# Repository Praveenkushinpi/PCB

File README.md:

# PCB
This is where i will share my learning in PCB designing  
#PLANE
✈️ Plane - My First PCB Design
Plane is my first custom PCB project, designed to simulate the lighting effect found on airplane wings. This simple circuit includes resistors, capacitors, and LEDs arranged to visually mimic wingtip lights, often used for orientation and safety on real aircraft.

🔧 Components Used

4 × Resistors 

2 × Capacitors 

2 × LEDs

2 × PNP transistors 
Power Source – 3V or 5V (battery or USB)

🔌 Functionality

The PCB is designed to:

Power multiple LEDs representing plane wing lights

Include basic passive components for voltage control and stability

Be compact and simple enough for beginners to fabricate and solder

The lights can be statically on or modified later with microcontroller logic to blink in patterns.

📐 Design Notes
Designed using [KiCad](https://www.kicad.org/)

All traces are routed for minimal interference

The layout resembles a small aircraft outline, with LEDs placed at the ends to simulate left and right wings

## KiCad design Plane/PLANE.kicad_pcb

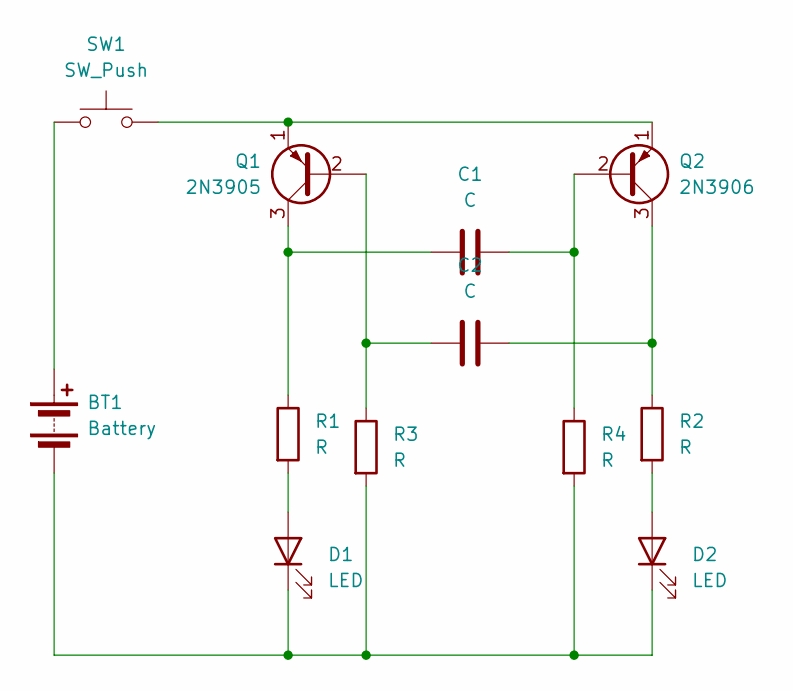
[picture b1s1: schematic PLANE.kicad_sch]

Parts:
BT1: Battery; BatteryHolder_Keystone_3034_1x20mm
C1, C2: C; CP_Radial_D8.0mm_P5.00mm
D1, D2: LED; LED_D5.0mm
Q1: 2N3905; TO-92_Inline
Q2: 2N3906; TO-92_Inline
R1, R2, R3, R4: R; R_Axial_DIN0207_L6.3mm_D2.5mm_P7.62mm_Horizontal
SW1: SW_Push; SW_PUSH_6mm

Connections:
unnamed: BT1.1 (+), SW1.1
unnamed: BT1.2 (-), D1.1 (K), D2.1 (K), R3.2, R4.2
unnamed: D1.2 (A), R1.2
unnamed: D2.2 (A), R2.2
unnamed: C2.2, Q1.2 (B), R3.1
unnamed: C1.1, Q1.3 (C), R1.1
unnamed: Q1.1 (E), Q2.1 (E), SW1.2
unnamed: C1.2, Q2.2 (B), R4.1
unnamed: C2.1, Q2.3 (C), R2.1

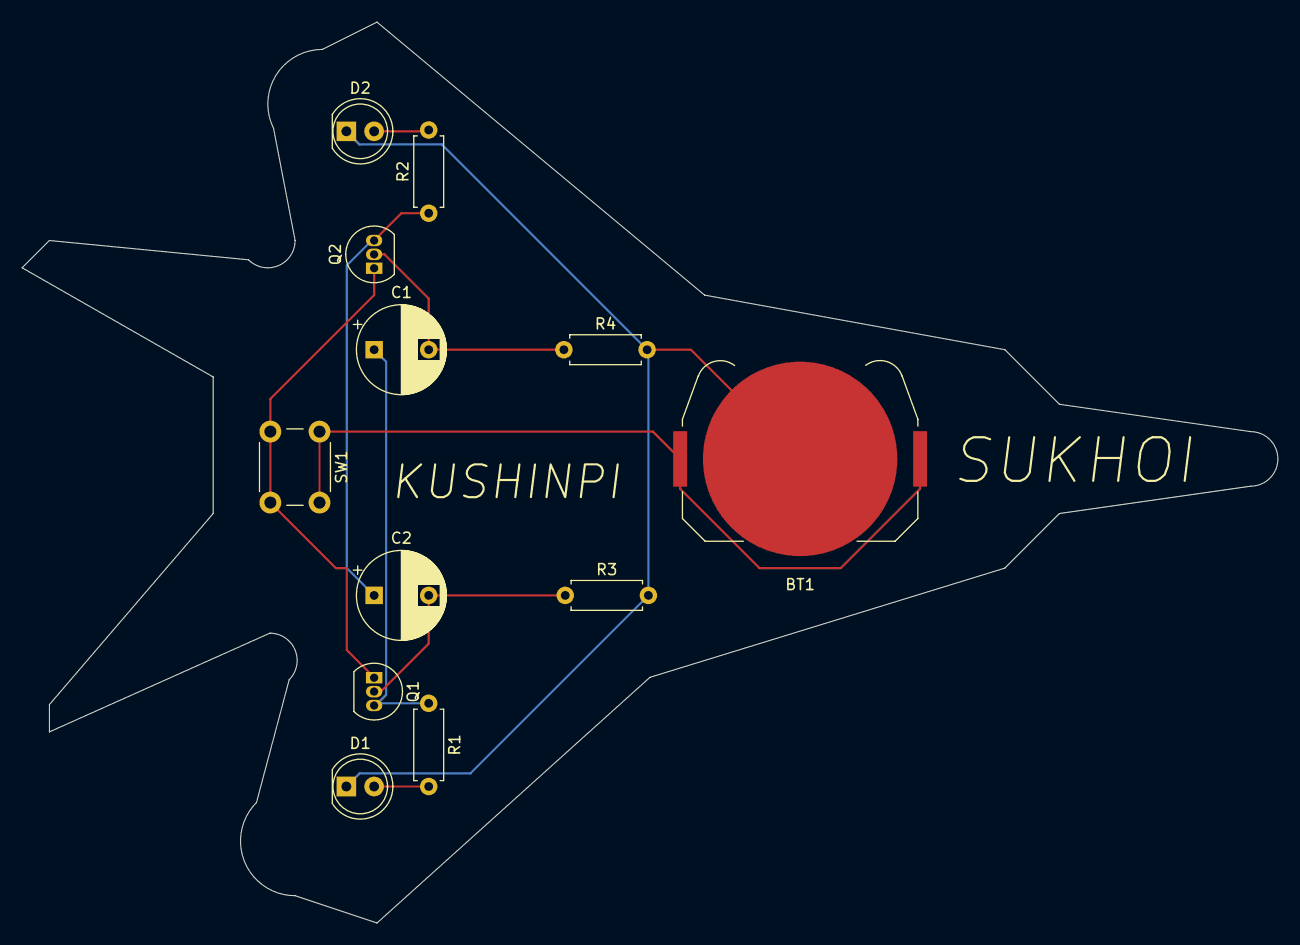
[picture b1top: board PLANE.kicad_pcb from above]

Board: 2 copper layers, 115.0 x 82.5 mm, 12 parts (0 on the bottom side), 9 nets.
